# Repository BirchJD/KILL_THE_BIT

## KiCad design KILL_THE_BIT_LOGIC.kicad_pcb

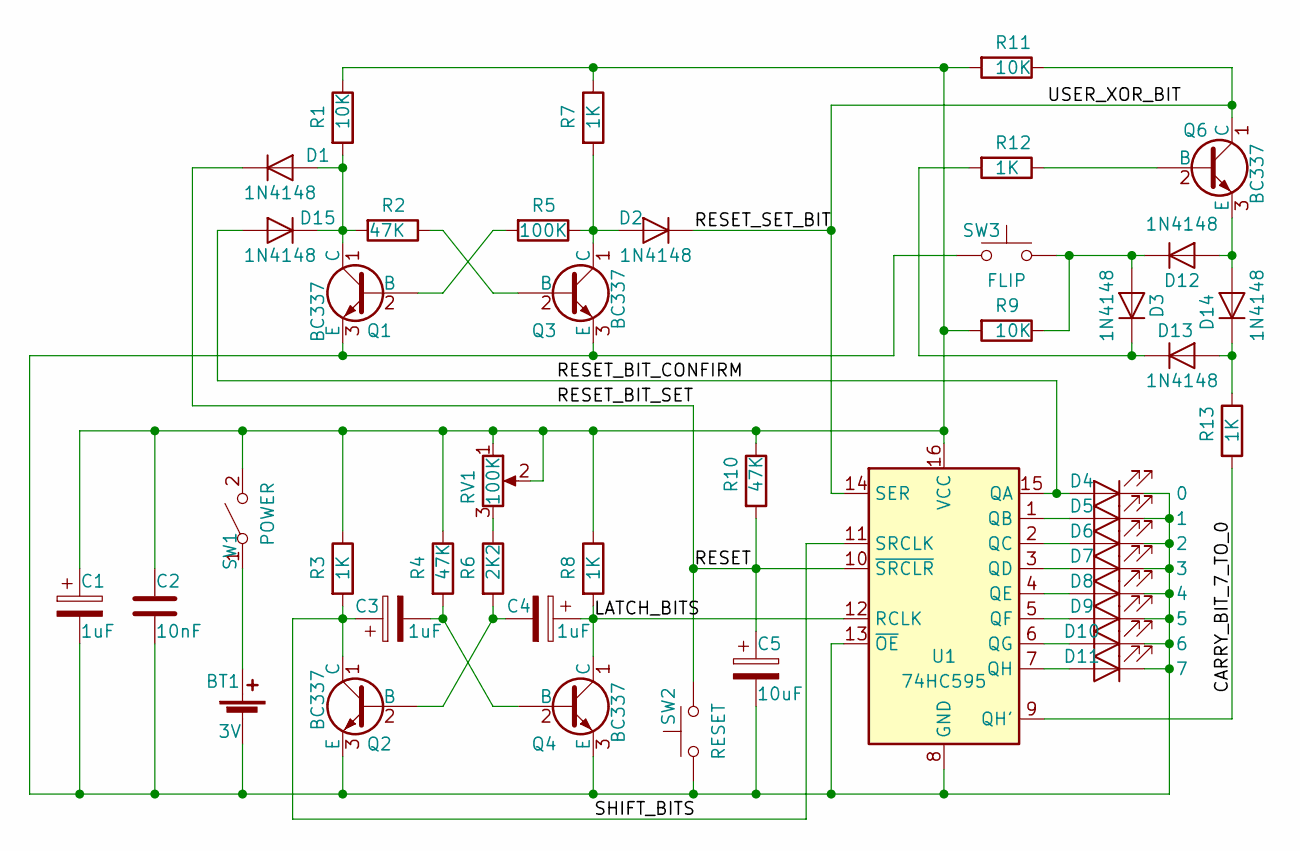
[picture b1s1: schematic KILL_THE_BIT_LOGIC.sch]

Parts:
BT1: 3V; BatteryHolder_Keystone_103_1x20mm
C1, C3, C4: 1uF; CP_Radial_D5.0mm_P2.50mm
C2: 10nF; C_Disc_D5.0mm_W2.5mm_P5.00mm
C5: 10uF; CP_Radial_D5.0mm_P2.50mm
D1, D2, D3, D12, D13, D14, D15: 1N4148; D_A-405_P10.16mm_Horizontal
D4: 0; LED_D3.0mm
D5: 1; LED_D3.0mm
D6: 2; LED_D3.0mm
D7: 3; LED_D3.0mm
D8: 4; LED_D3.0mm
D9: 5; LED_D3.0mm
D10: 6; LED_D3.0mm
D11: 7; LED_D3.0mm
Q1, Q2, Q3, Q4, Q6: BC337; TO-92L_Wide
R1, R9, R11: 10K; R_Axial_DIN0207_L6.3mm_D2.5mm_P10.16mm_Horizontal
R2, R4, R10: 47K; R_Axial_DIN0207_L6.3mm_D2.5mm_P10.16mm_Horizontal
R3, R7, R8, R12, R13: 1K; R_Axial_DIN0207_L6.3mm_D2.5mm_P10.16mm_Horizontal
R5: 100K; R_Axial_DIN0207_L6.3mm_D2.5mm_P10.16mm_Horizontal
R6: 2K2; R_Axial_DIN0207_L6.3mm_D2.5mm_P10.16mm_Horizontal
RV1: 100K; Potentiometer_Runtron_RM-065_Vertical
SW1: POWER; SWITCH_SPDT
SW2: RESET; SW_PUSH_6mm
SW3: FLIP; SW_PUSH_6mm
U1: 74HC595; DIP-16_W7.62mm_LongPads

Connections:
/CARRY_BIT_7_TO_0: R13.2, U1.9 (QH')
/LATCH_BITS: C4.1, Q4.1 (C), R8.2, U1.12 (RCLK)
/RESET: C5.1, D1.1 (K), R10.2, SW2.2, U1.10 (~SRCLR)
/RESET_BIT_CONFIRM: D4.2 (A), D15.2 (A), U1.15 (QA)
/RESET_SET_BIT: D2.1 (K), Q6.1 (C), R11.1, U1.14 (SER)
/SHIFT_BITS: C3.1, Q2.1 (C), R3.2, U1.11 (SRCLK)
unnamed: BT1.1 (+), SW1.1 (A)
unnamed: BT1.2 (-), C1.2, C2.2, C5.2, D4.1 (K), D5.1 (K), D6.1 (K), D7.1 (K), D8.1 (K), D9.1 (K), D10.1 (K), D11.1 (K), Q1.3 (E), Q2.3 (E), Q3.3 (E), Q4.3 (E), SW2.1, SW3.1, U1.8 (GND), U1.13 (~OE)
unnamed: C1.1, C2.1, R1.1, R3.1, R4.1, R7.1, R8.1, R9.2, R10.1, R11.2, RV1.1, RV1.2, SW1.2 (B), U1.16 (VCC)
unnamed: C3.2, Q4.2 (B), R4.2
unnamed: C4.2, Q2.2 (B), R6.2
unnamed: D1.2 (A), D15.1 (K), Q1.1 (C), R1.2, R2.2
unnamed: D2.2 (A), Q3.1 (C), R5.1, R7.2
unnamed: D5.2 (A), U1.1 (QB)
unnamed: D6.2 (A), U1.2 (QC)
unnamed: D7.2 (A), U1.3 (QD)
unnamed: D8.2 (A), U1.4 (QE)
unnamed: D9.2 (A), U1.5 (QF)
unnamed: D10.2 (A), U1.6 (QG)
unnamed: D11.2 (A), U1.7 (QH)
unnamed: D3.2 (A), D12.1 (K), R9.1, SW3.2
unnamed: D12.2 (A), D14.2 (A), Q6.3 (E)
unnamed: D3.1 (K), D13.1 (K), R12.2
unnamed: D13.2 (A), D14.1 (K), R13.1
unnamed: Q1.2 (B), R5.2
unnamed: Q3.2 (B), R2.1
unnamed: Q6.2 (B), R12.1
unnamed: R6.1, RV1.3

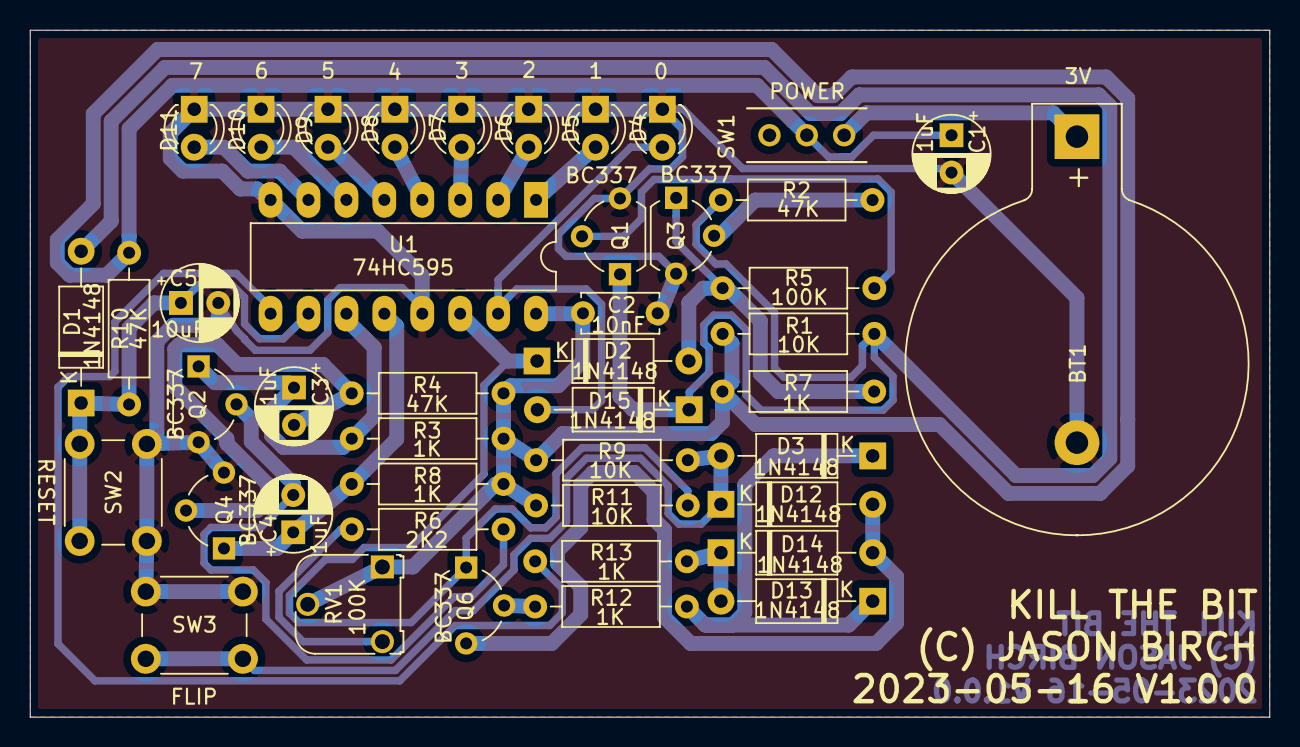
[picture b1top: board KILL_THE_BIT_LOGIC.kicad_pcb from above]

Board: 2 copper layers, 83.0 x 46.0 mm, 44 parts (0 on the bottom side), 28 nets.

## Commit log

2023-05-20 Project PCB gerber and pdf files. Project pdf circuit diagram.
2025-02-18 Updated resistor value to latch within resistor 10% tolerance.
